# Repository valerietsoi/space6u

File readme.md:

# space6u

just kidding, despite the surplus of 3u and 6u caps i actually had to buy stabs for both sizes...

untested

## pics
| | |
| --- | --- |
|  |   |
|  |   |

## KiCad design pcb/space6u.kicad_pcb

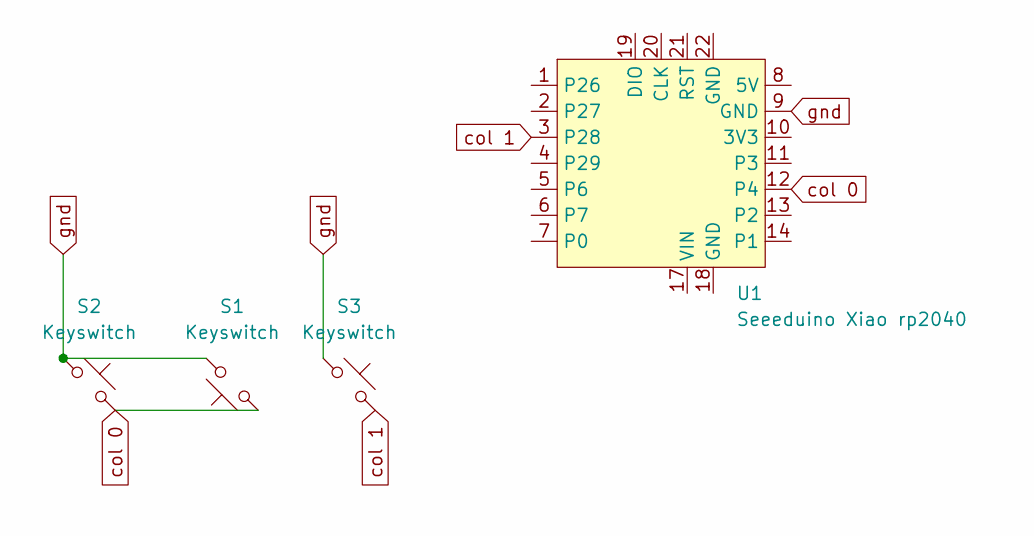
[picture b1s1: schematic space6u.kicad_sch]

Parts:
S1: Keyswitch; SW_Hotswap_Kailh_MX_Plated_6.00u
S2, S3: Keyswitch; Hotswap_MX_Plated_3.00u
U1: Seeeduino Xiao rp2040; Xiao_rp2040_ACH

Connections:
col 0: S1.1, S2.2, U1.12 (P4)
col 1: S3.2, U1.3 (P28)
gnd: S1.2, S2.1, S3.1, U1.9 (GND)

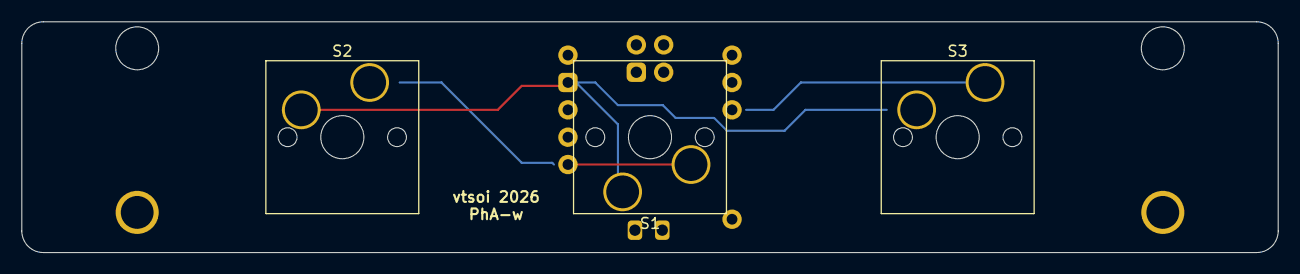
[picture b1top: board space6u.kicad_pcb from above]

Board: 2 copper layers, 116.7 x 21.4 mm, 4 parts (1 on the bottom side), 3 nets.

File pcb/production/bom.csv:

Designator,Footprint,Quantity,Value,LCSC Part #
S1,SW_Hotswap_Kailh_MX_Plated_6.00u,1,Keyswitch,
"S2, S3",Hotswap_MX_Plated_3.00u,2,Keyswitch,

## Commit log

2026-03-17 first draft untested
2026-03-19 plate and case files
2026-03-19 readme
2026-03-19 renders added
